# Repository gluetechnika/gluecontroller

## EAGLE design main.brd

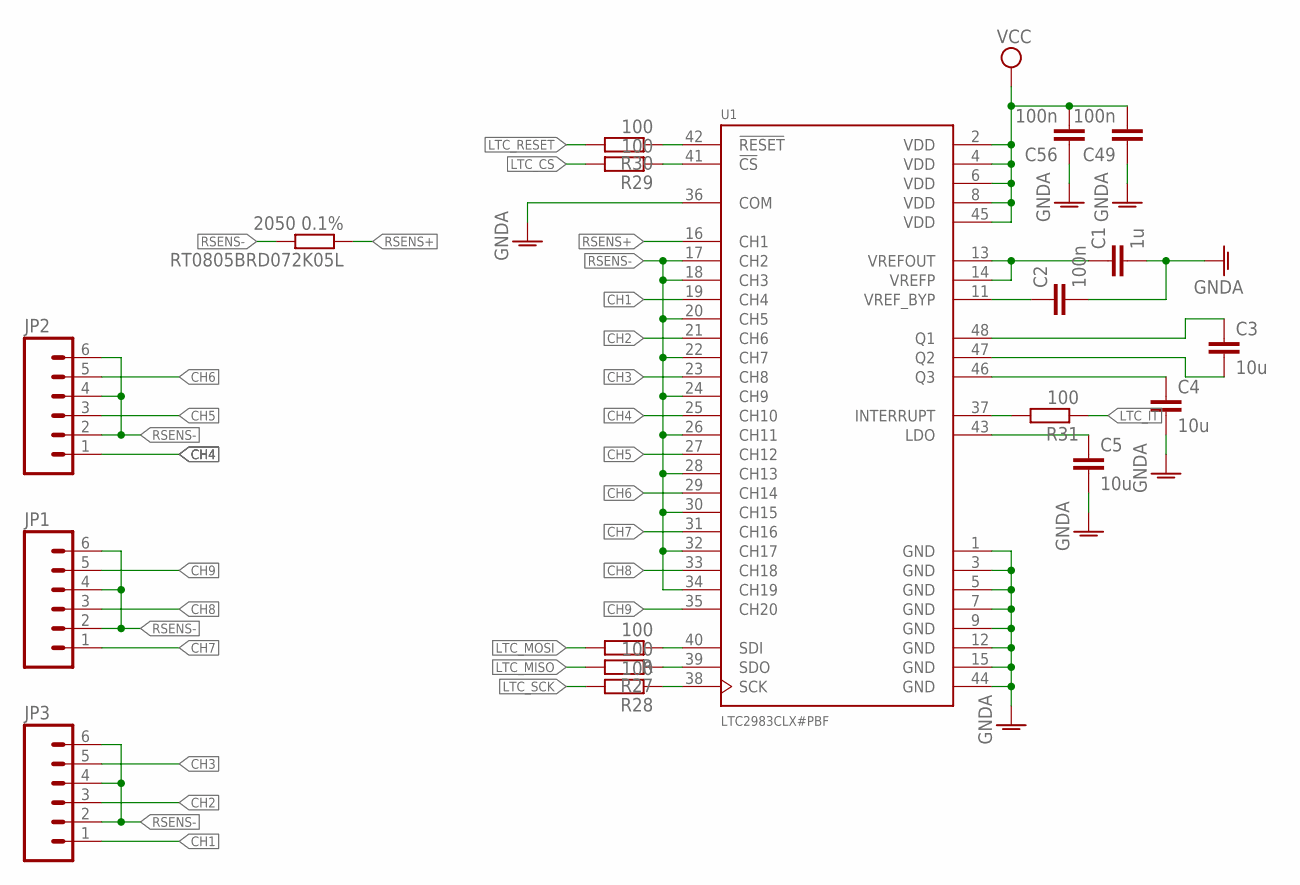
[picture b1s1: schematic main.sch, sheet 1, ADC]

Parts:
C1: 1u; C0603K
C2, C49, C56: 100n; C0603K
C3, C4, C5: 10u; C0805K
JP1, JP2, JP3: M063.5MM-6; SCREWTERMINAL-3.5MM-6
R, R27, R28, R29, R30, R31: 100; R0603
RT0805BRD072K05L: 2050 0.1%; R0805
U1: LTC2983CLX#PBF; QFP50P900X900X160-48N

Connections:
CH1: JP3.1, U1.19 (CH4)
CH2: JP3.3, U1.21 (CH6)
CH3: JP3.5, U1.23 (CH8)
CH4: JP2.1, U1.25 (CH10)
CH5: JP2.3, U1.27 (CH12)
CH6: JP2.5, U1.29 (CH14)
CH7: JP1.1, U1.31 (CH16)
CH8: JP1.3, U1.33 (CH18)
CH9: JP1.5, U1.35 (CH20)
GNDA: C1.2, C2.2, C4.2, C5.2, C49.1, C56.1, U1.1 (GND), U1.3 (GND), U1.5 (GND), U1.7 (GND), U1.9 (GND), U1.12 (GND), U1.15 (GND), U1.36 (COM), U1.44 (GND); also elsewhere on the board
LTC_CS: R29.2; also elsewhere on the board
LTC_IT: R31.1; also elsewhere on the board
LTC_MISO: R27.2; also elsewhere on the board
LTC_MOSI: R.2; also elsewhere on the board
LTC_RESET: R30.2; also elsewhere on the board
LTC_SCK: R28.2; also elsewhere on the board
unnamed: R31.2, U1.37 (INTERRUPT)
unnamed: C1.1, U1.13 (VREFOUT), U1.14 (VREFP)
unnamed: C2.1, U1.11 (VREF_BYP)
unnamed: C3.1, U1.48 (Q1)
unnamed: C3.2, U1.47 (Q2)
unnamed: C4.1, U1.46 (Q3)
unnamed: C5.1, U1.43 (LDO)
unnamed: R30.1, U1.42 (!RESET!)
unnamed: R29.1, U1.41 (!CS!)
unnamed: R.1, U1.40 (SDI)
unnamed: R27.1, U1.39 (SDO)
unnamed: R28.1, U1.38 (SCK)
RSENS+: RT0805BRD072K05L.1, U1.16 (CH1)
RSENS-: JP1.2, JP1.4, JP1.6, JP2.2, JP2.4, JP2.6, JP3.2, JP3.4, JP3.6, RT0805BRD072K05L.2, U1.17 (CH2), U1.18 (CH3), U1.20 (CH5), U1.22 (CH7), U1.24 (CH9), U1.26 (CH11), U1.28 (CH13), U1.30 (CH15), U1.32 (CH17), U1.34 (CH19)
VCC: C49.2, C56.2, U1.2 (VDD), U1.4 (VDD), U1.6 (VDD), U1.8 (VDD), U1.45 (VDD); also elsewhere on the board

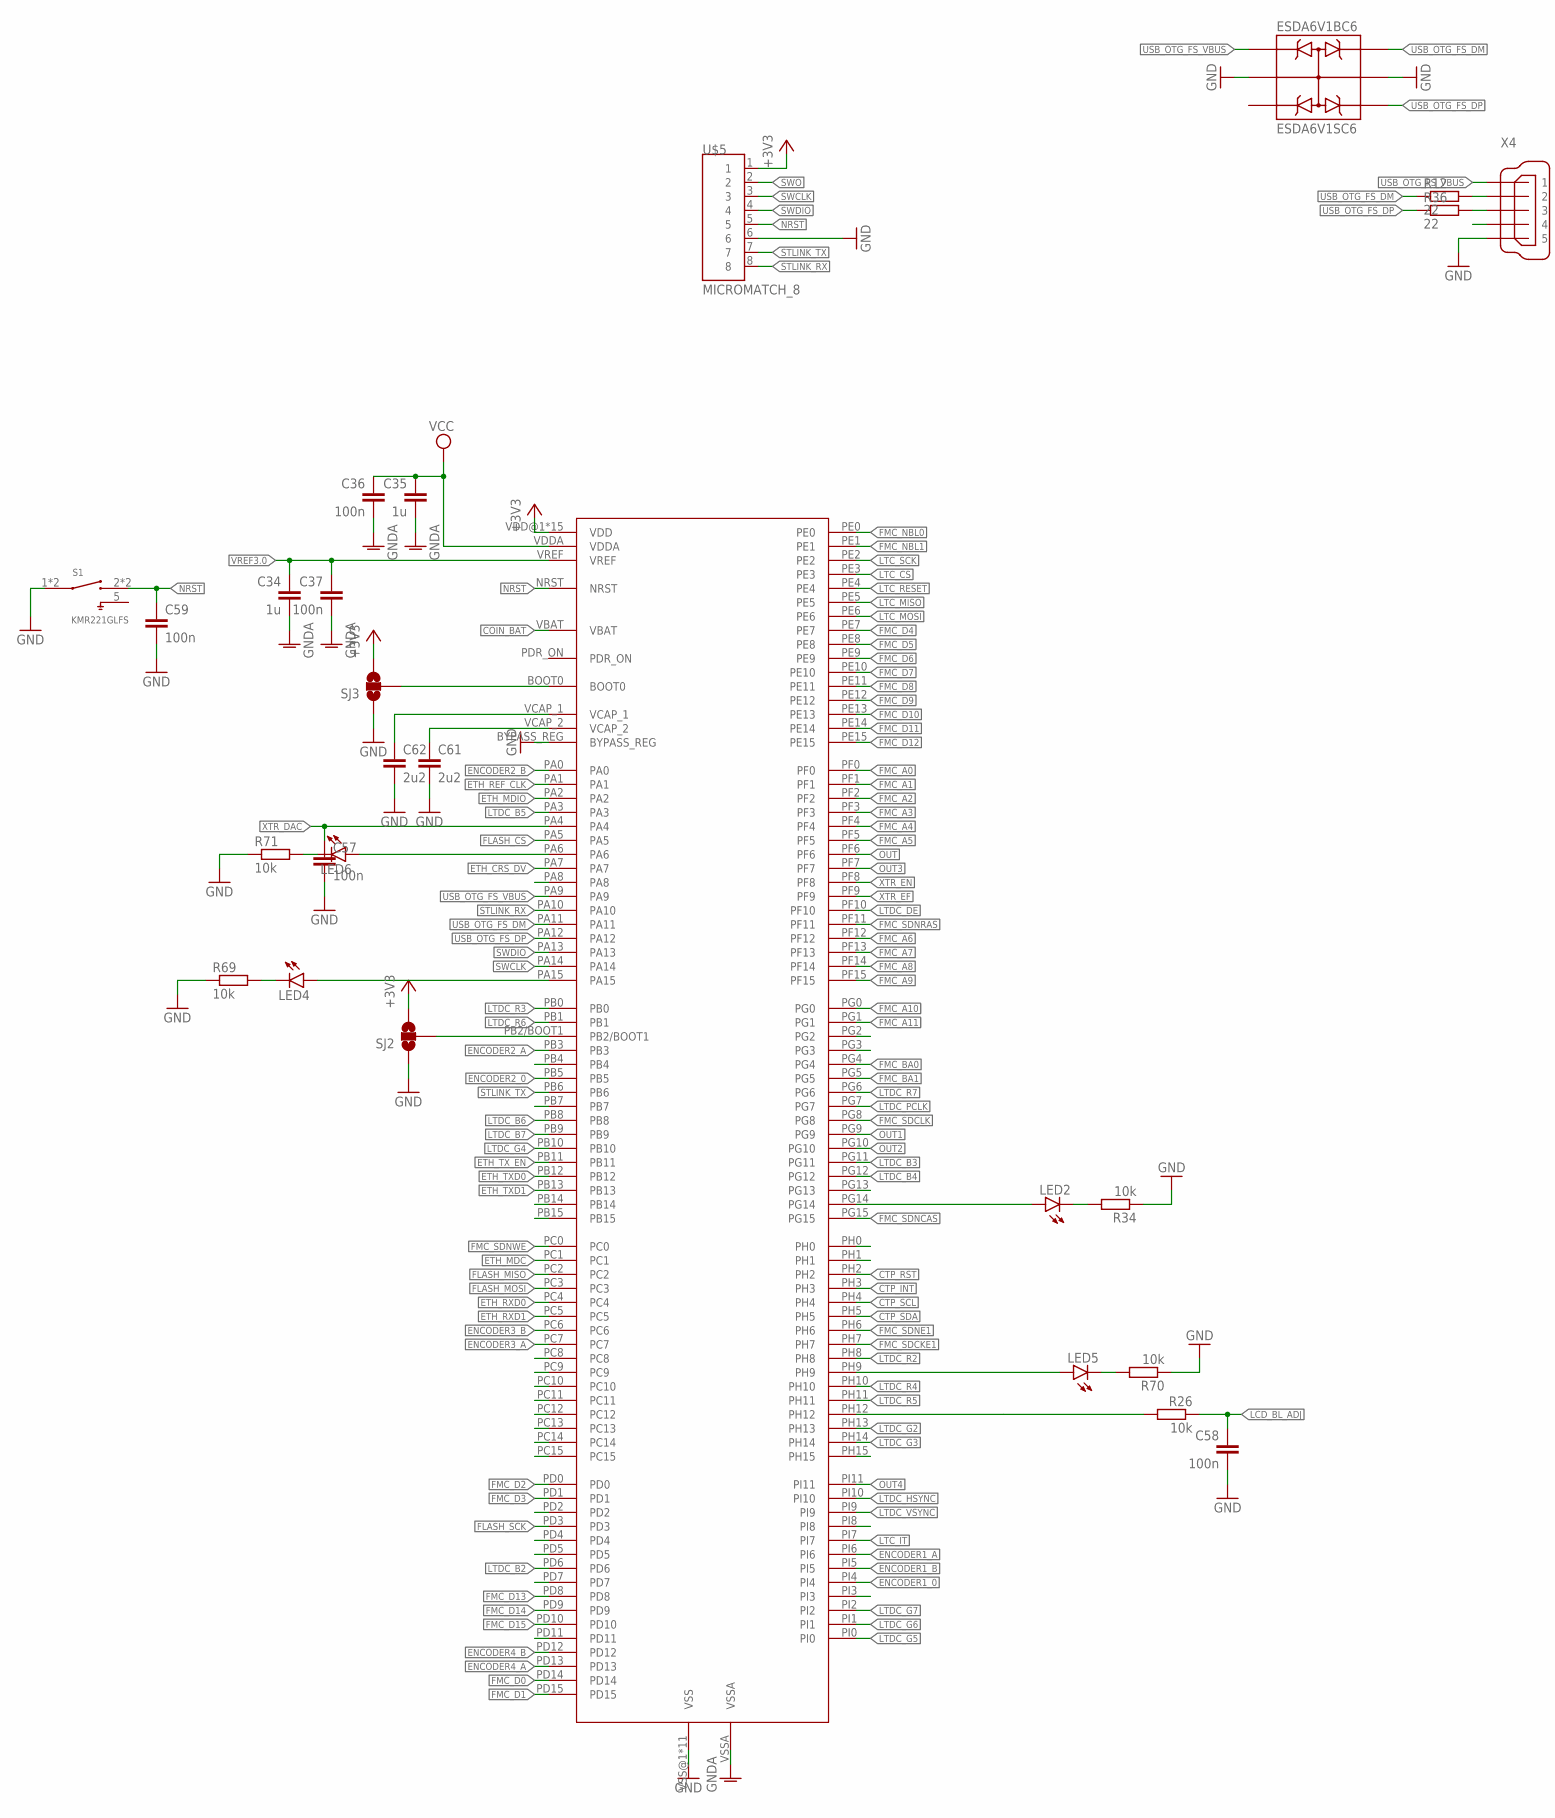
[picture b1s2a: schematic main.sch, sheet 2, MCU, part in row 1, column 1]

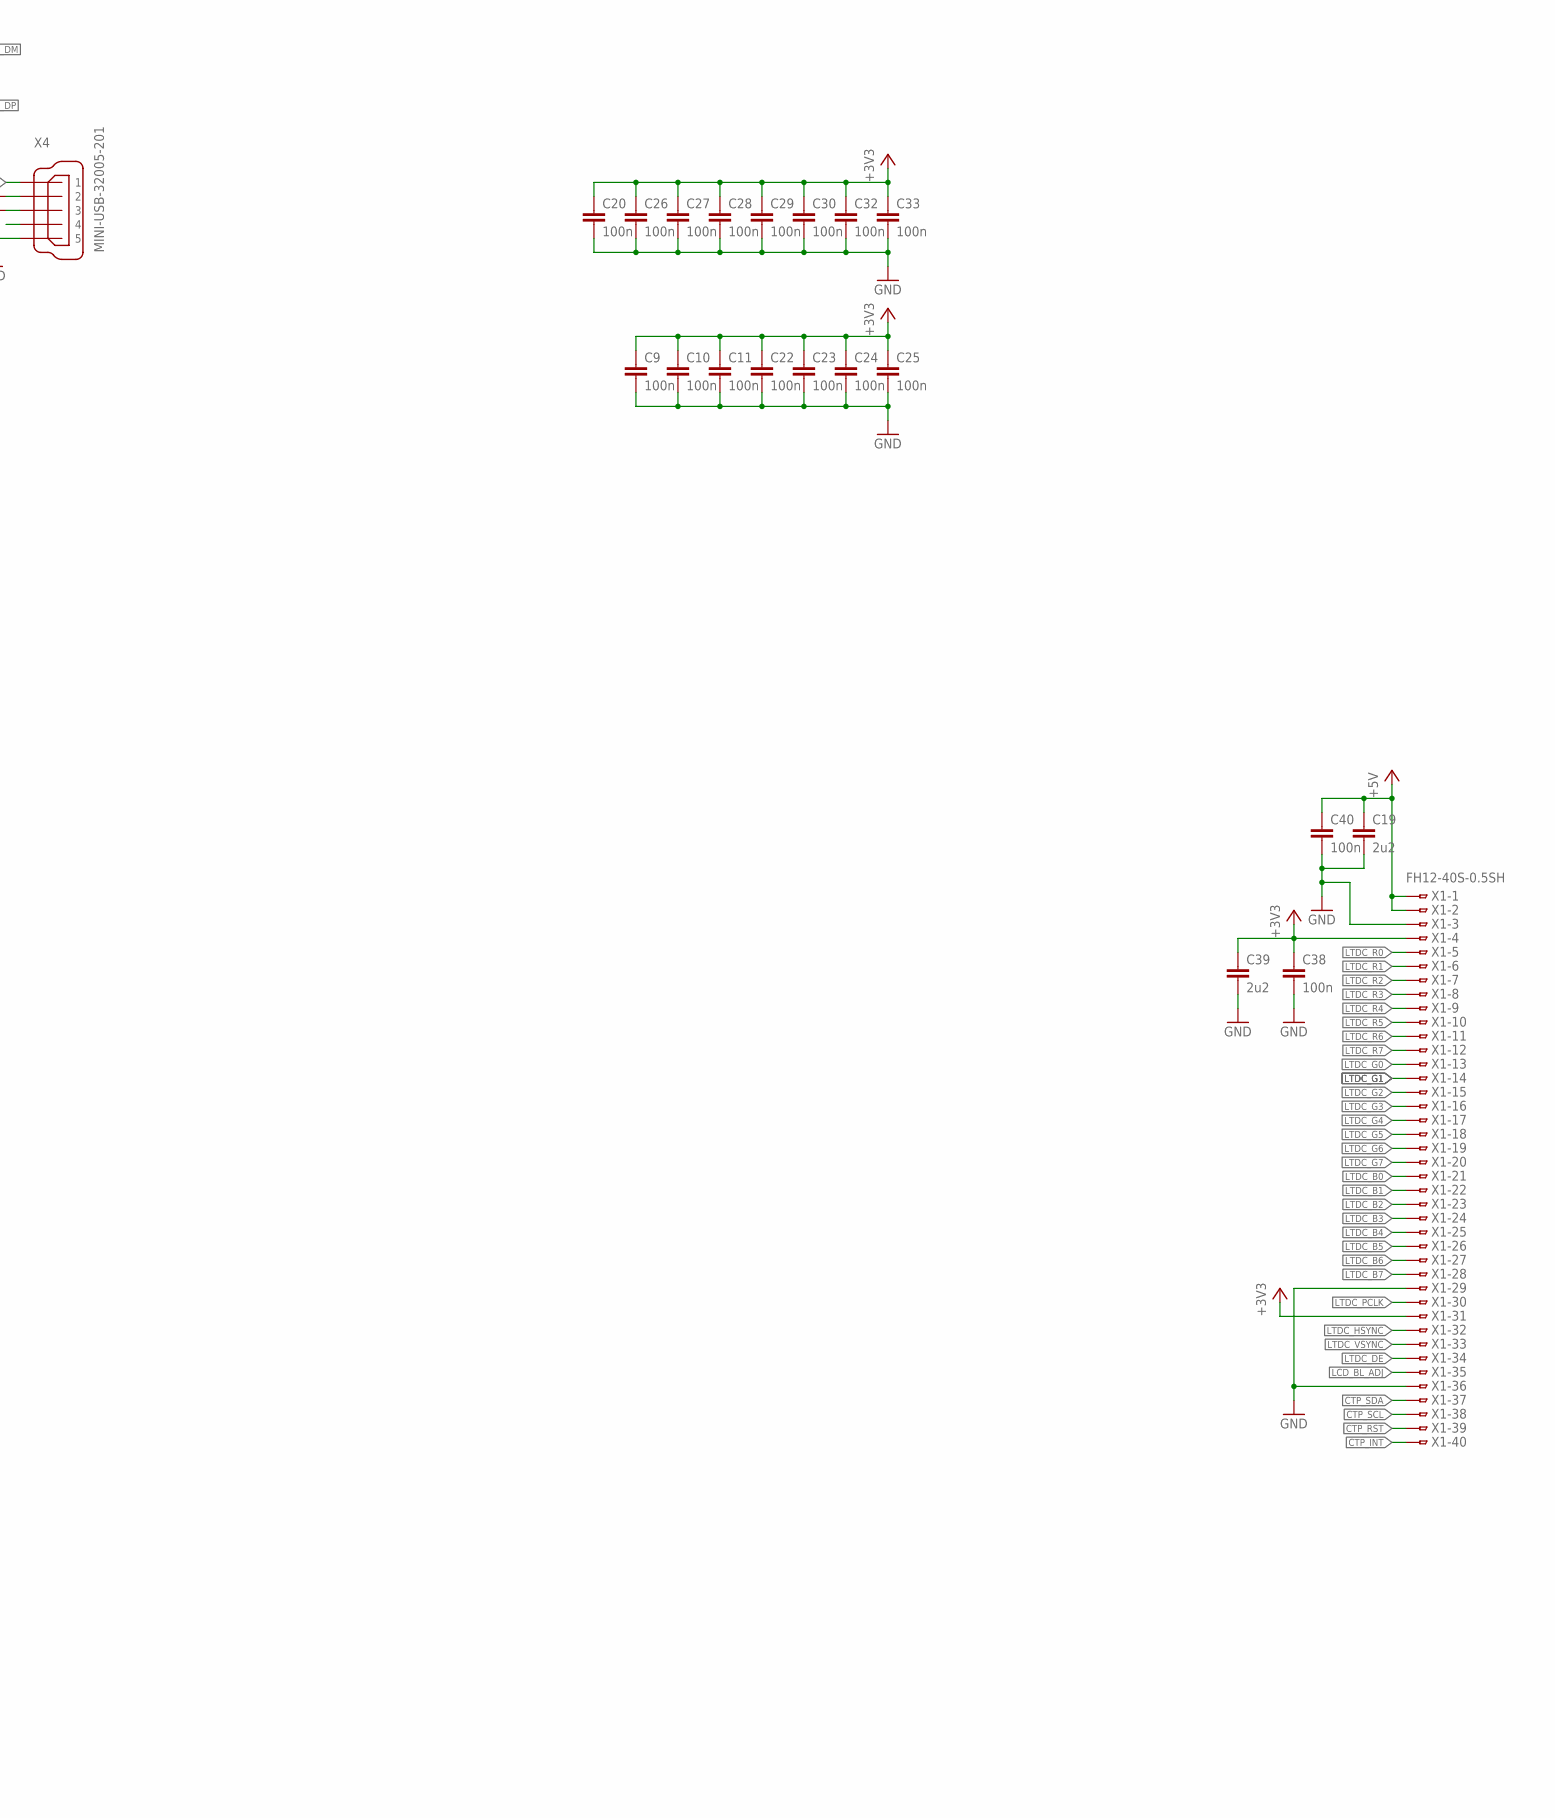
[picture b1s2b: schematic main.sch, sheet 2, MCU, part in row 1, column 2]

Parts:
C9, C10, C11, C20, C22, C23, C24, C25, C26, C27, C28, C29, C30, C32, C33, C36, C37, C57, C58, C59: 100n; C0603K
C19, C39, C61, C62: 2u2; C0805K
C34, C35: 1u; C0805K
C38, C40: 100n; C0805
ESDA6V1BC6: ESDA6V1SC6; SOT95P280X145-6N
LED2, LED4, LED5, LED6: LEDCHIPLED_0603; CHIPLED_0603
R12, R36: 22; R0603
R26, R34, R69, R70, R71: 10k; R0603
S1: KMR221GLFS; SW_KMR221GLFS
SJ2, SJ3: SOLDERJUMPER_2WAYS; SJ_3
U$3: STM32F429_176; QFP50P2600X2600X160-176N
U$5: MICROMATCH_8
X1: FH12-40S-0.5SH
X4: MINI-USB-32005-201; 32005-201

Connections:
+3V3: C9.1, C10.1, C11.1, C20.1, C22.1, C23.1, C24.1, C25.1, C26.1, C27.1, C28.1, C29.1, C30.1, C32.1, C33.1, C38.1, C39.1, SJ2.3, SJ3.3, U$3.VDD@1 (VDD), U$3.VDD@2 (VDD), U$3.VDD@3 (VDD), U$3.VDD@4 (VDD), U$3.VDD@5 (VDD), U$3.VDD@6 (VDD), U$3.VDD@7 (VDD), U$3.VDD@8 (VDD), U$3.VDD@9 (VDD), U$3.VDD@10 (VDD), U$3.VDD@11 (VDD), U$3.VDD@12 (VDD), U$3.VDD@13 (VDD), U$3.VDD@14 (VDD), U$3.VDD@15 (VDD), U$5.1, X1.4, X1.31; also elsewhere on the board
+5V: C19.1, C40.1, X1.1, X1.2; also elsewhere on the board
COIN_BAT: U$3.VBAT; also elsewhere on the board
CTP_INT: U$3.PH3, X1.40
CTP_RST: U$3.PH2, X1.39
CTP_SCL: U$3.PH4, X1.38
CTP_SDA: U$3.PH5, X1.37
ENCODER1_0: U$3.PI4; also elsewhere on the board
ENCODER1_A: U$3.PI6; also elsewhere on the board
ENCODER1_B: U$3.PI5; also elsewhere on the board
ENCODER2_0: U$3.PB5; also elsewhere on the board
ENCODER2_A: U$3.PB3; also elsewhere on the board
ENCODER2_B: U$3.PA0; also elsewhere on the board
ENCODER3_A: U$3.PC7
ENCODER3_B: U$3.PC6
ENCODER4_A: U$3.PD13
ENCODER4_B: U$3.PD12
ETH_CRS_DV: U$3.PA7; also elsewhere on the board
ETH_MDC: U$3.PC1; also elsewhere on the board
ETH_MDIO: U$3.PA2; also elsewhere on the board
ETH_REF_CLK: U$3.PA1; also elsewhere on the board
ETH_RXD0: U$3.PC4; also elsewhere on the board
ETH_RXD1: U$3.PC5; also elsewhere on the board
ETH_TXD0: U$3.PB12; also elsewhere on the board
ETH_TXD1: U$3.PB13; also elsewhere on the board
ETH_TX_EN: U$3.PB11; also elsewhere on the board
FLASH_CS: U$3.PA5; also elsewhere on the board
FLASH_MISO: U$3.PC2; also elsewhere on the board
FLASH_MOSI: U$3.PC3; also elsewhere on the board
FLASH_SCK: U$3.PD3; also elsewhere on the board
FMC_A0: U$3.PF0; also elsewhere on the board
FMC_A1: U$3.PF1; also elsewhere on the board
FMC_A2: U$3.PF2; also elsewhere on the board
FMC_A3: U$3.PF3; also elsewhere on the board
FMC_A4: U$3.PF4; also elsewhere on the board
FMC_A5: U$3.PF5; also elsewhere on the board
FMC_A6: U$3.PF12; also elsewhere on the board
FMC_A7: U$3.PF13; also elsewhere on the board
FMC_A8: U$3.PF14; also elsewhere on the board
FMC_A9: U$3.PF15; also elsewhere on the board
FMC_A10: U$3.PG0; also elsewhere on the board
FMC_A11: U$3.PG1; also elsewhere on the board
FMC_BA0: U$3.PG4; also elsewhere on the board
FMC_BA1: U$3.PG5; also elsewhere on the board
FMC_D0: U$3.PD14; also elsewhere on the board
FMC_D1: U$3.PD15; also elsewhere on the board
FMC_D2: U$3.PD0; also elsewhere on the board
FMC_D3: U$3.PD1; also elsewhere on the board
FMC_D4: U$3.PE7; also elsewhere on the board
FMC_D5: U$3.PE8; also elsewhere on the board
FMC_D6: U$3.PE9; also elsewhere on the board
FMC_D7: U$3.PE10; also elsewhere on the board
FMC_D8: U$3.PE11; also elsewhere on the board
FMC_D9: U$3.PE12; also elsewhere on the board
FMC_D10: U$3.PE13; also elsewhere on the board
FMC_D11: U$3.PE14; also elsewhere on the board
FMC_D12: U$3.PE15; also elsewhere on the board
FMC_D13: U$3.PD8; also elsewhere on the board
FMC_D14: U$3.PD9; also elsewhere on the board
FMC_D15: U$3.PD10; also elsewhere on the board
FMC_NBL0: U$3.PE0; also elsewhere on the board
FMC_NBL1: U$3.PE1; also elsewhere on the board
FMC_SDCKE1: U$3.PH7; also elsewhere on the board
FMC_SDCLK: U$3.PG8; also elsewhere on the board
FMC_SDNCAS: U$3.PG15; also elsewhere on the board
FMC_SDNE1: U$3.PH6; also elsewhere on the board
FMC_SDNRAS: U$3.PF11; also elsewhere on the board
FMC_SDNWE: U$3.PC0; also elsewhere on the board
GND: C9.2, C10.2, C11.2, C19.2, C20.2, C22.2, C23.2, C24.2, C25.2, C26.2, C27.2, C28.2, C29.2, C30.2, C32.2, C33.2, C38.2, C39.2, C40.2, C57.2, C58.2, C59.2, C61.2, C62.2, ESDA6V1BC6.2, ESDA6V1BC6.5, R34.1, R69.1, R70.1, R71.1, S1.1, S1.4 (1), SJ2.1, SJ3.1, U$3.BYPASS_REG, U$3.VSS@1 (VSS), U$3.VSS@2 (VSS), U$3.VSS@3 (VSS), U$3.VSS@4 (VSS), U$3.VSS@5 (VSS), U$3.VSS@7 (VSS), U$3.VSS@8 (VSS), U$3.VSS@9 (VSS), U$3.VSS@10 (VSS), U$3.VSS@11 (VSS), U$3.VSS@12 (VSS), U$5.6, X1.3, X1.29, X1.36, X4.5; also elsewhere on the board
GNDA: C34.2, C35.2, C36.2, C37.2, U$3.VSSA; also elsewhere on the board
LCD_BL_ADJ: C58.1, R26.1, X1.35
LTC_CS: U$3.PE3; also elsewhere on the board
LTC_IT: U$3.PI7; also elsewhere on the board
LTC_MISO: U$3.PE5; also elsewhere on the board
LTC_MOSI: U$3.PE6; also elsewhere on the board
LTC_RESET: U$3.PE4; also elsewhere on the board
LTC_SCK: U$3.PE2; also elsewhere on the board
LTDC_B0: X1.21
LTDC_B1: X1.22
LTDC_B2: U$3.PD6, X1.23
LTDC_B3: U$3.PG11, X1.24
LTDC_B4: U$3.PG12, X1.25
LTDC_B5: U$3.PA3, X1.26
LTDC_B6: U$3.PB8, X1.27
LTDC_B7: U$3.PB9, X1.28
LTDC_DE: U$3.PF10, X1.34
LTDC_G0: X1.13
LTDC_G1: X1.14
LTDC_G2: U$3.PH13, X1.15
LTDC_G3: U$3.PH14, X1.16
LTDC_G4: U$3.PB10, X1.17
LTDC_G5: U$3.PI0, X1.18
LTDC_G6: U$3.PI1, X1.19
LTDC_G7: U$3.PI2, X1.20
LTDC_HSYNC: U$3.PI10, X1.32
LTDC_PCLK: U$3.PG7, X1.30
LTDC_R0: X1.5
LTDC_R1: X1.6
LTDC_R2: U$3.PH8, X1.7
LTDC_R3: U$3.PB0, X1.8
LTDC_R4: U$3.PH10, X1.9
LTDC_R5: U$3.PH11, X1.10
LTDC_R6: U$3.PB1, X1.11
LTDC_R7: U$3.PG6, X1.12
LTDC_VSYNC: U$3.PI9, X1.33
unnamed: LED4.A, U$3.PA15
unnamed: LED6.A, U$3.PA6
unnamed: R12.2, X4.2
unnamed: R36.2, X4.3
unnamed: LED2.A, U$3.PG14
unnamed: LED4.C, R69.2
unnamed: LED2.C, R34.2
unnamed: SJ3.2, U$3.BOOT0
unnamed: C62.1, U$3.VCAP_1
unnamed: C61.1, U$3.VCAP_2
unnamed: LED5.A, U$3.PH9
unnamed: SJ2.2, U$3.PB2/BOOT1
unnamed: LED5.C, R70.2
unnamed: LED6.C, R71.2
unnamed: R26.2, U$3.PH12
NRST: C59.1, S1.2 (3), S1.3, U$3.NRST, U$5.5; also elsewhere on the board
OUT: U$3.PF6; also elsewhere on the board
OUT1: U$3.PG9; also elsewhere on the board
OUT2: U$3.PG10; also elsewhere on the board
OUT3: U$3.PF7; also elsewhere on the board
OUT4: U$3.PI11; also elsewhere on the board
STLINK_RX: U$3.PA10, U$5.8
STLINK_TX: U$3.PB6, U$5.7
SWCLK: U$3.PA14, U$5.3
SWDIO: U$3.PA13, U$5.4
SWO: U$5.2
USB_OTG_FS_DM: ESDA6V1BC6.6, R12.1, U$3.PA11
USB_OTG_FS_DP: ESDA6V1BC6.4, R36.1, U$3.PA12
USB_OTG_FS_VBUS: ESDA6V1BC6.1, U$3.PA9, X4.1
VCC: C35.1, C36.1, U$3.VDDA; also elsewhere on the board
VREF3.0: C34.1, C37.1, U$3.VREF; also elsewhere on the board
XTR_DAC: C57.1, U$3.PA4; also elsewhere on the board
XTR_EF: U$3.PF9; also elsewhere on the board
XTR_EN: U$3.PF8; also elsewhere on the board

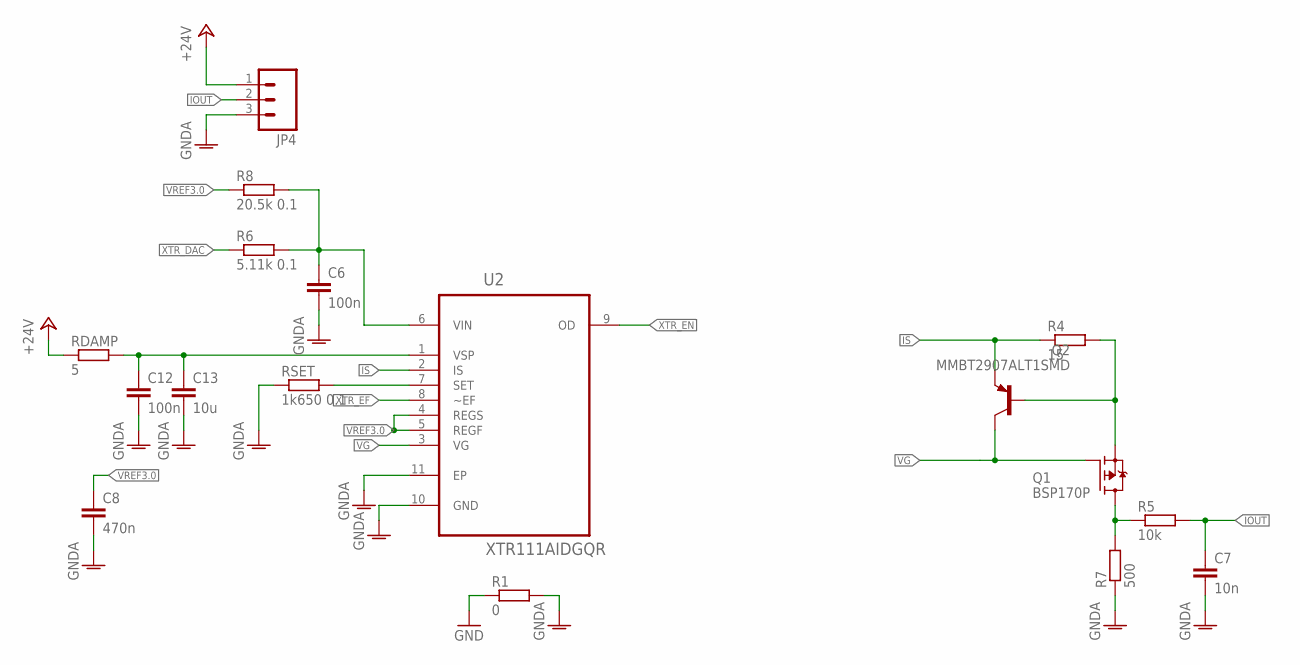
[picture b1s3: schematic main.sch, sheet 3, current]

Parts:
C6, C12: 100n; C0603K
C7: 10n; C0603K
C8: 470n; C0603K
C13: 10u; C0805
JP4: M03SCREW; SCREWTERMINAL-3.5MM-3
Q1: BSP170P; SOT223
Q2: MMBT2907ALT1SMD; SOT23-BEC
R1: 0; R0603
R4: 15; R0603
R5: 10k; R0603
R6: 5.11k 0.1; R0805
R7: 500; R0603
R8: 20.5k 0.1; R0805
RDAMP: 5; R0603
RSET: 1k650 0.1; R0805
U2: XTR111AIDGQR; SOP50P490X120-15N

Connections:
+24V: JP4.1, RDAMP.1; also elsewhere on the board
GND: R1.1; also elsewhere on the board
GNDA: C6.2, C7.2, C8.2, C12.2, C13.2, JP4.3, R1.2, R7.1, RSET.1, U2.10 (GND), U2.11 (EP); also elsewhere on the board
IOUT: C7.1, JP4.2, R5.2
IS: Q2.E, R4.1, U2.2 (IS)
unnamed: Q1.3 (S), Q2.B, R4.2
unnamed: C12.1, C13.1, RDAMP.2, U2.1 (VSP)
unnamed: Q1.2 (D), Q1.4 (D), R5.1, R7.2
unnamed: RSET.2, U2.7 (SET)
unnamed: C6.1, R6.2, R8.2, U2.6 (VIN)
VG: Q1.1 (G), Q2.C, U2.3 (VG)
VREF3.0: C8.1, R8.1, U2.4 (REGS), U2.5 (REGF); also elsewhere on the board
XTR_DAC: R6.1; also elsewhere on the board
XTR_EF: U2.8 (~EF); also elsewhere on the board
XTR_EN: U2.9 (OD); also elsewhere on the board

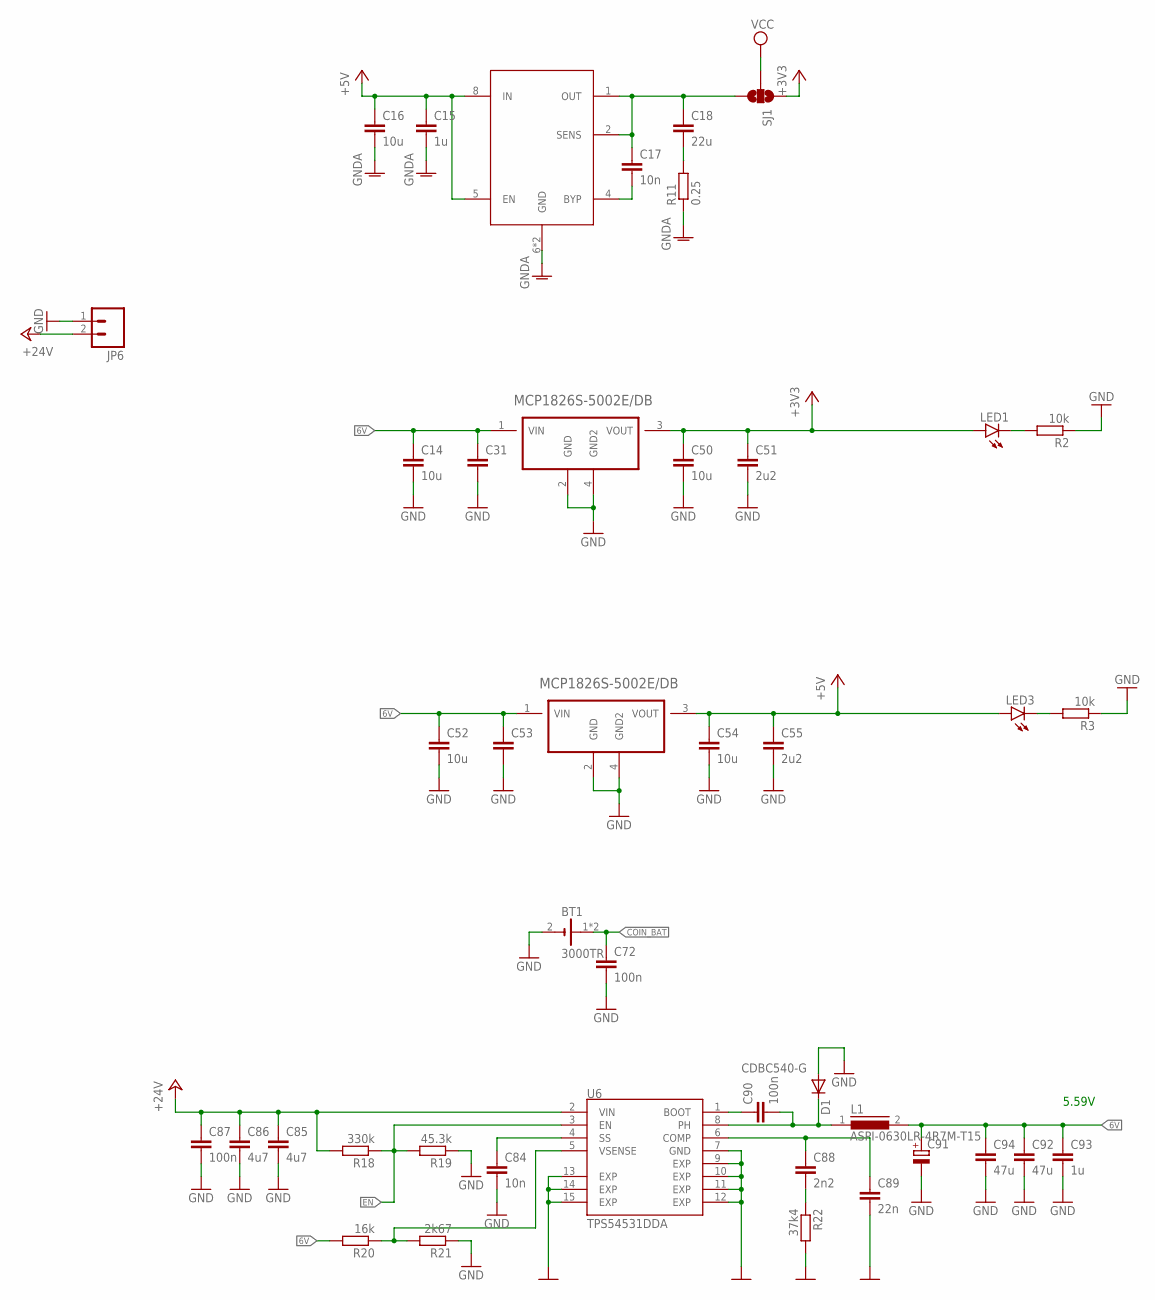
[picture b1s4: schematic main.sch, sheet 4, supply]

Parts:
BT1: 3000TR; BAT_3000TR
C14, C50, C52, C54: 10u; C0805K
C15: 1u; C0805
C16: 10u; C0805
C17, C84: 10n; C0603K
C18: 22u; C1206
C31, C53: C-EUC0805K; C0805K
C51, C55: 2u2; C0805K
C72, C87, C90: 100n; C0603K
C85, C86: 4u7; C0805K
C88: 2n2; C0603K
C89: 22n; C0603K
C91: CPOL-EUE5-6; E5-6
C92, C94: 47u; C1210
C93: 1u; C0603K
D1: CDBC540-G; SMB
JP6: M023.5MM-NO_SILK; SCREWTERMINAL-3.5MM-2-NS
L1: ASPI-0630LR-4R7M-T15; DR74
LED1, LED3: LEDCHIPLED_0603; CHIPLED_0603
R2, R3: 10k; R0603
R11: 0.25; R0603
R18: 330k; R0603
R19: 45.3k; R0603
R20: 16k; R0603
R21: 2k67; R0603
R22: 37k4; R0603
SJ1: SOLDERJUMPER_2WAYS; SJ_3
U3, U5: MCP1826S-5002E/DB; SOT230P700X180-4N
U6: TPS54531DDA; SOIC127P600X170-9N
U$2: IFX5444; SOIC8

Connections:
6V: C14.1, C31.1, C52.1, C53.1, C91.+, C92.1, C93.1, C94.1, L1.2, R20.2, U3.1 (VIN), U5.1 (VIN)
!EN: R18.1, R19.2, U6.3 (EN)
+3V3: C50.1, C51.1, LED1.A, SJ1.1, U3.3 (VOUT); also elsewhere on the board
+5V: C15.1, C16.1, C54.1, C55.1, LED3.A, U5.3 (VOUT), U$2.5 (EN), U$2.8 (IN); also elsewhere on the board
+24V: C85.1, C86.1, C87.1, JP6.2, R18.2, U6.2 (VIN); also elsewhere on the board
COIN_BAT: BT1.1 (+), BT1.3 (+), C72.1; also elsewhere on the board
GND: BT1.2 (-), C14.2, C31.2, C50.2, C51.2, C52.2, C53.2, C54.2, C55.2, C72.2, C84.2, C85.2, C86.2, C87.2, C89.2, C91.-, C92.2, C93.2, C94.2, D1.A, JP6.1, R2.1, R3.1, R19.1, R21.1, R22.2, U3.2 (GND), U3.4 (GND2), U5.2 (GND), U5.4 (GND2), U6.7 (GND), U6.9 (EXP), U6.10 (EXP), U6.11 (EXP), U6.12 (EXP), U6.13 (EXP), U6.14 (EXP), U6.15 (EXP); also elsewhere on the board
GNDA: C15.2, C16.2, R11.1, U$2.6 (GND), U$2.E (GND); also elsewhere on the board
unnamed: C18.2, R11.2
unnamed: C17.2, U$2.4 (BYP)
unnamed: C17.1, C18.1, SJ1.3, U$2.1 (OUT), U$2.2 (SENS)
unnamed: LED1.C, R2.2
unnamed: R20.1, R21.2, U6.5 (VSENSE)
unnamed: C84.1, U6.4 (SS)
unnamed: C88.1, C89.1, U6.6 (COMP)
unnamed: C88.2, R22.1
unnamed: C90.1, U6.1 (BOOT)
unnamed: C90.2, D1.C, L1.1, U6.8 (PH)
unnamed: LED3.C, R3.2
VCC: SJ1.2; also elsewhere on the board

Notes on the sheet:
5.59V

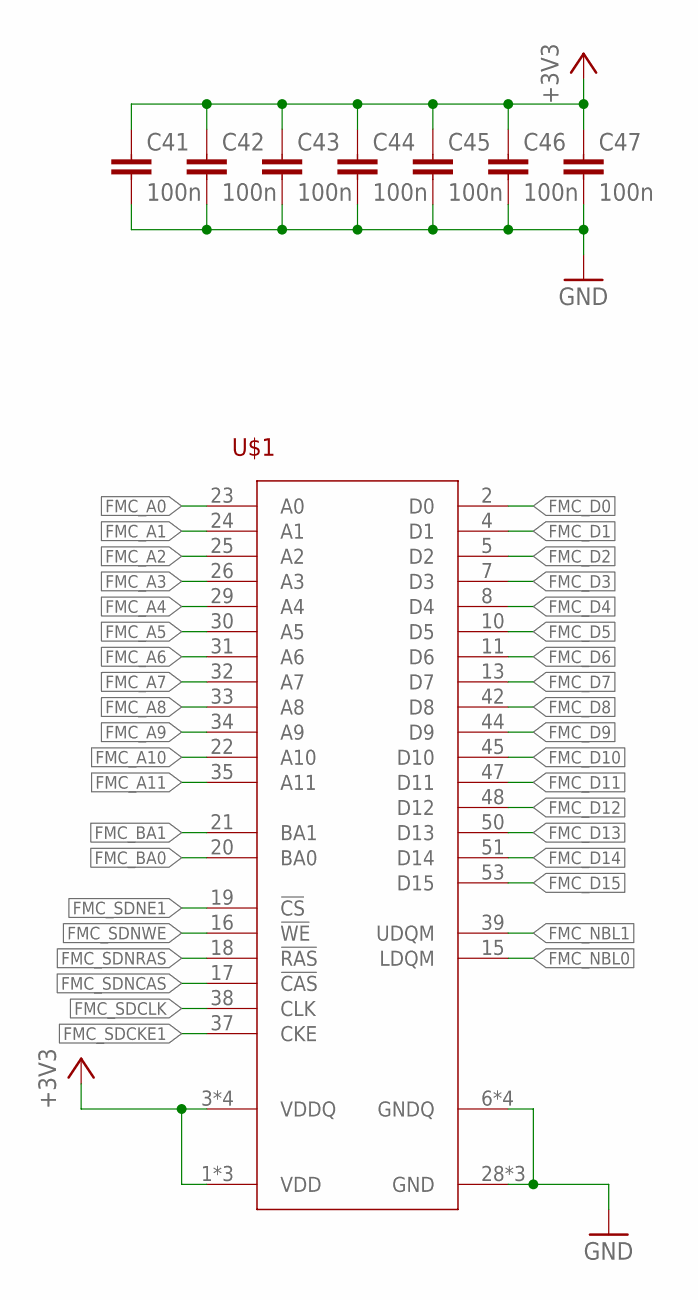
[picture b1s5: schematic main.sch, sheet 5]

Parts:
C41, C42, C43, C44, C45, C46, C47: 100n; C0603K
U$1: IS45S16400J; TSOP54

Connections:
+3V3: C41.1, C42.1, C43.1, C44.1, C45.1, C46.1, C47.1, U$1.1 (VDD), U$1.3 (VDDQ), U$1.9 (VDDQ), U$1.14 (VDD), U$1.27 (VDD), U$1.43 (VDDQ), U$1.49 (VDDQ); also elsewhere on the board
FMC_A0: U$1.23 (A0); also elsewhere on the board
FMC_A1: U$1.24 (A1); also elsewhere on the board
FMC_A2: U$1.25 (A2); also elsewhere on the board
FMC_A3: U$1.26 (A3); also elsewhere on the board
FMC_A4: U$1.29 (A4); also elsewhere on the board
FMC_A5: U$1.30 (A5); also elsewhere on the board
FMC_A6: U$1.31 (A6); also elsewhere on the board
FMC_A7: U$1.32 (A7); also elsewhere on the board
FMC_A8: U$1.33 (A8); also elsewhere on the board
FMC_A9: U$1.34 (A9); also elsewhere on the board
FMC_A10: U$1.22 (A10); also elsewhere on the board
FMC_A11: U$1.35 (A11); also elsewhere on the board
FMC_BA0: U$1.20 (BA0); also elsewhere on the board
FMC_BA1: U$1.21 (BA1); also elsewhere on the board
FMC_D0: U$1.2 (D0); also elsewhere on the board
FMC_D1: U$1.4 (D1); also elsewhere on the board
FMC_D2: U$1.5 (D2); also elsewhere on the board
FMC_D3: U$1.7 (D3); also elsewhere on the board
FMC_D4: U$1.8 (D4); also elsewhere on the board
FMC_D5: U$1.10 (D5); also elsewhere on the board
FMC_D6: U$1.11 (D6); also elsewhere on the board
FMC_D7: U$1.13 (D7); also elsewhere on the board
FMC_D8: U$1.42 (D8); also elsewhere on the board
FMC_D9: U$1.44 (D9); also elsewhere on the board
FMC_D10: U$1.45 (D10); also elsewhere on the board
FMC_D11: U$1.47 (D11); also elsewhere on the board
FMC_D12: U$1.48 (D12); also elsewhere on the board
FMC_D13: U$1.50 (D13); also elsewhere on the board
FMC_D14: U$1.51 (D14); also elsewhere on the board
FMC_D15: U$1.53 (D15); also elsewhere on the board
FMC_NBL0: U$1.15 (LDQM); also elsewhere on the board
FMC_NBL1: U$1.39 (UDQM); also elsewhere on the board
FMC_SDCKE1: U$1.37 (CKE); also elsewhere on the board
FMC_SDCLK: U$1.38 (CLK); also elsewhere on the board
FMC_SDNCAS: U$1.17 (!CAS); also elsewhere on the board
FMC_SDNE1: U$1.19 (!CS); also elsewhere on the board
FMC_SDNRAS: U$1.18 (!RAS); also elsewhere on the board
FMC_SDNWE: U$1.16 (!WE); also elsewhere on the board
GND: C41.2, C42.2, C43.2, C44.2, C45.2, C46.2, C47.2, U$1.6 (GNDQ), U$1.12 (GNDQ), U$1.28 (GND), U$1.41 (GND), U$1.46 (GNDQ), U$1.52 (GNDQ), U$1.54 (GND); also elsewhere on the board

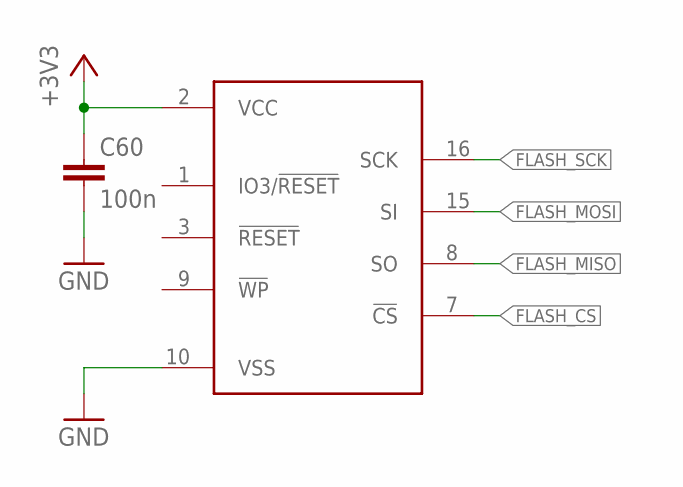
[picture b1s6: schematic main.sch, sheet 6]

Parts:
C60: 100n; C0603K
U$4: S25FLX; SOIC16

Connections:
+3V3: C60.1, U$4.2 (VCC); also elsewhere on the board
FLASH_CS: U$4.7 (!CS); also elsewhere on the board
FLASH_MISO: U$4.8 (SO); also elsewhere on the board
FLASH_MOSI: U$4.15 (SI); also elsewhere on the board
FLASH_SCK: U$4.16 (SCK); also elsewhere on the board
GND: C60.2, U$4.10 (VSS); also elsewhere on the board

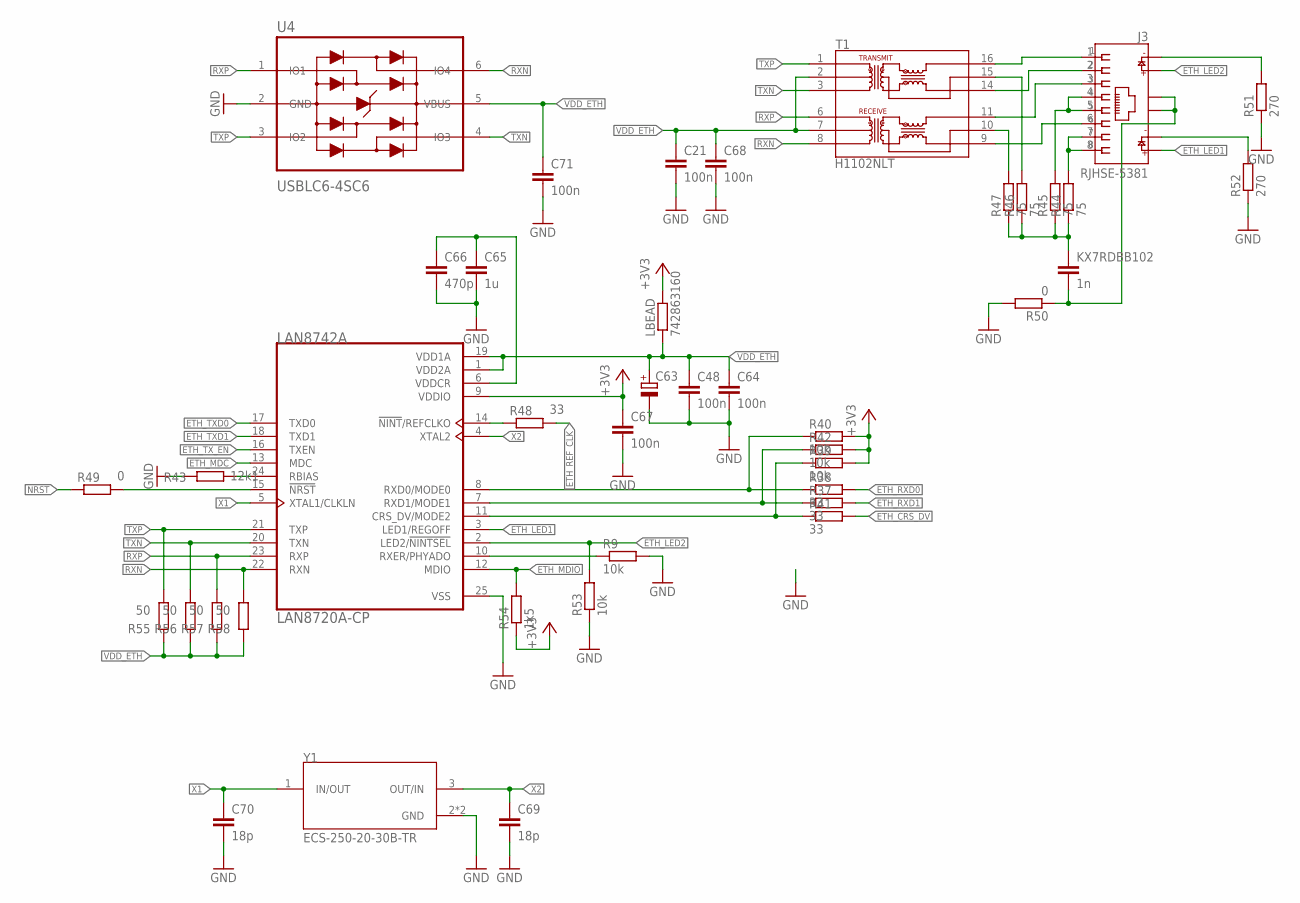
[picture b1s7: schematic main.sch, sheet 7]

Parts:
C21, C48, C64, C67, C68, C71: 100n; C0603K
C63: CPOL-EUSMCA; SMC_A
C65: 1u; C0603K
C66: 470p; C0603K
C69, C70: 18p; C0603K
J3: RJHSE-5381; AMPHENOL_RJHSE-5381
KX7RDBB102: 1n; C1206K
LAN8742A: LAN8720A-CP; QFN50P400X400X100-25N
LBEAD: 742863160; R0603
R9, R39, R40, R42, R53: 10k; R0603
R37, R38, R41, R48: 33; R0603
R43: 12k1; R0603
R44, R45, R46, R47: 75; R0603
R49, R50: 0; R0603
R51, R52: 270; R0603
R54: 1k5; R0603
R55, R56, R57, R58: 50; R0603
T1: H1102NLT; XFMR_H1102NLT
U4: USBLC6-4SC6; SOT95P280X145-6N
Y1: ECS-250-20-30B-TR; XTAL_ECS-250-20-30B-TR

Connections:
+3V3: C67.1, LAN8742A.9 (VDDIO), LBEAD.2, R39.2, R40.2, R42.2, R54.1; also elsewhere on the board
ETH_CRS_DV: R41.2; also elsewhere on the board
ETH_LED1: J3.12, LAN8742A.3 (LED1/REGOFF)
ETH_LED2: J3.10, LAN8742A.2 (LED2/!NINTSEL!), R53.2
ETH_MDC: LAN8742A.13 (MDC); also elsewhere on the board
ETH_MDIO: LAN8742A.12 (MDIO), R54.2; also elsewhere on the board
ETH_REF_CLK: R48.2; also elsewhere on the board
ETH_RXD0: R38.2; also elsewhere on the board
ETH_RXD1: R37.2; also elsewhere on the board
ETH_TXD0: LAN8742A.17 (TXD0); also elsewhere on the board
ETH_TXD1: LAN8742A.18 (TXD1); also elsewhere on the board
ETH_TX_EN: LAN8742A.16 (TXEN); also elsewhere on the board
GND: C21.2, C48.2, C63.-, C64.2, C65.2, C66.2, C67.2, C68.2, C69.2, C70.2, C71.2, LAN8742A.25 (VSS), R9.2, R43.1, R50.2, R51.1, R52.1, R53.1, U4.2 (GND), Y1.2 (GND), Y1.4 (GND); also elsewhere on the board
unnamed: LAN8742A.8 (RXD0/MODE0), R38.1, R40.1
unnamed: LAN8742A.10 (RXER/PHYADO), R9.1
unnamed: LAN8742A.11 (CRS_DV/MODE2), R39.1, R41.1
unnamed: J3.4, J3.5, R45.2
unnamed: R47.2, T1.10
unnamed: J3.S1, J3.S2, KX7RDBB102.2, R50.1
unnamed: J3.9, R51.2
unnamed: LAN8742A.7 (RXD1/MODE1), R37.1, R42.1
unnamed: LAN8742A.14 (!NINT!/REFCLKO), R48.1
unnamed: C65.1, C66.1, LAN8742A.6 (VDDCR)
unnamed: LAN8742A.24 (RBIAS), R43.2
unnamed: J3.7, J3.8, R44.2
unnamed: KX7RDBB102.1, R44.1, R45.1, R46.1, R47.1
unnamed: LAN8742A.15 (!NRST), R49.2
unnamed: J3.1, T1.16
unnamed: R46.2, T1.15
unnamed: J3.2, T1.14
unnamed: J3.3, T1.11
unnamed: J3.6, T1.9
unnamed: J3.11, R52.2
NRST: R49.1; also elsewhere on the board
RXN: LAN8742A.22 (RXN), R58.2, T1.8, U4.6 (IO4)
RXP: LAN8742A.23 (RXP), R57.2, T1.6, U4.1 (IO1)
TXN: LAN8742A.20 (TXN), R56.2, T1.3, U4.4 (IO3)
TXP: LAN8742A.21 (TXP), R55.2, T1.1, U4.3 (IO2)
VDD_ETH: C21.1, C48.1, C63.+, C64.1, C68.1, C71.1, LAN8742A.1 (VDD2A), LAN8742A.19 (VDD1A), LBEAD.1, R55.1, R56.1, R57.1, R58.1, T1.2, T1.7, U4.5 (VBUS)
X1: C70.1, LAN8742A.5 (XTAL1/CLKLN), Y1.1 (IN/OUT)
X2: C69.1, LAN8742A.4 (XTAL2), Y1.3 (OUT/IN)

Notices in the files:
parts and their libraries:
SparkFun: Licensing: CC v3.0 Share-Alike You are welcome to use this library for commercial purposes.
